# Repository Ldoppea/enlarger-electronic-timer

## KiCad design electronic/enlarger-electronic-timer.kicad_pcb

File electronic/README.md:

# Electronic for enlarger-electronic-timer

## Resources

Arduino Mini library downloaded from http://kicadhowto.org/LibLib.htm

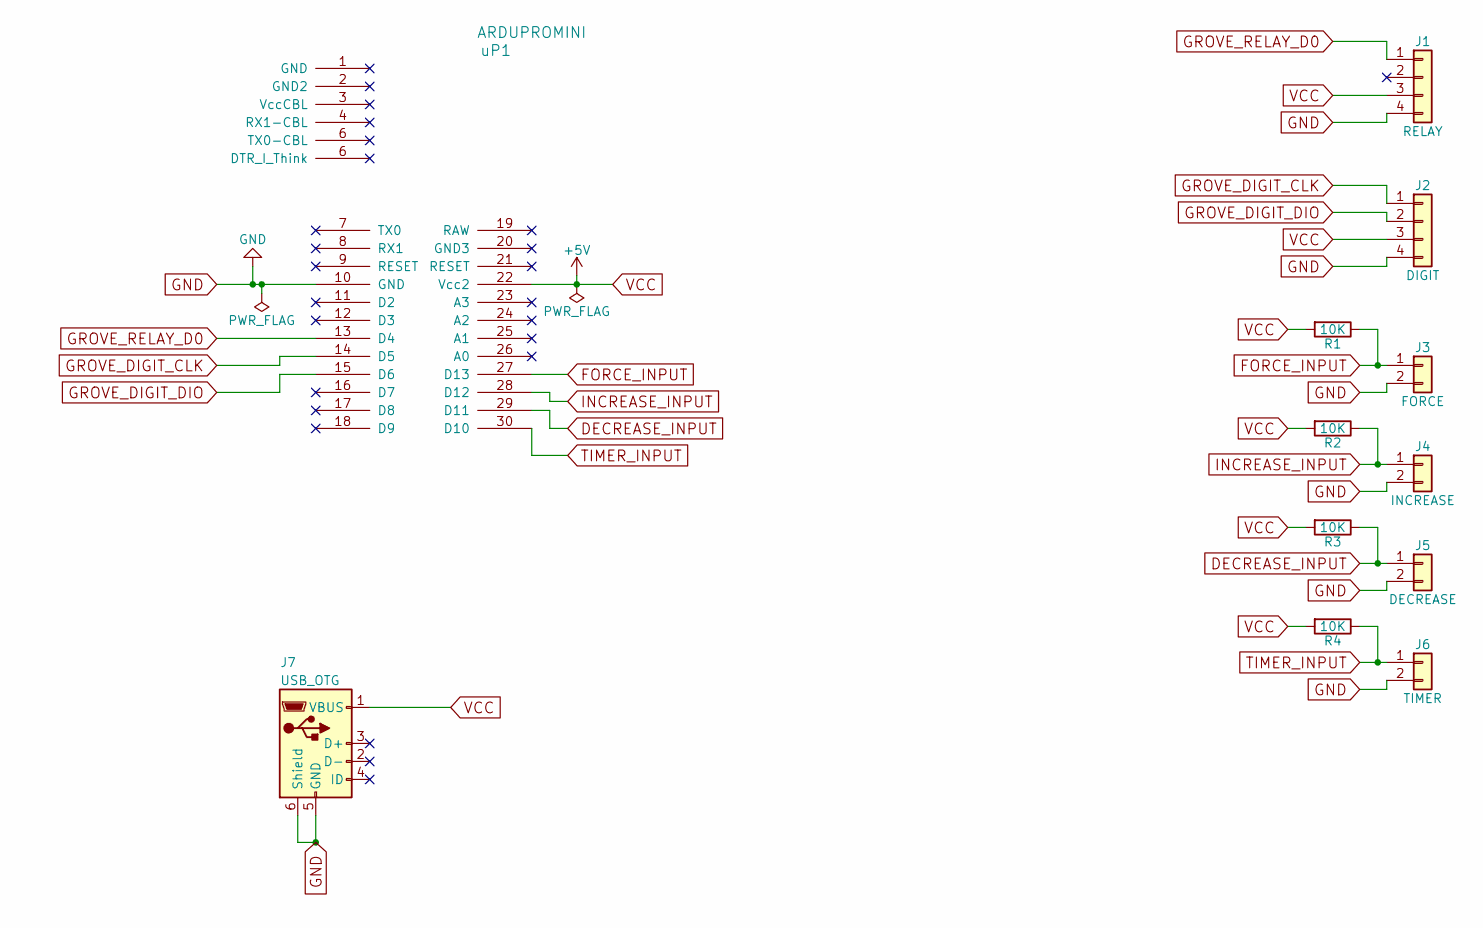
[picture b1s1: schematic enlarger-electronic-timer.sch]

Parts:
J1: RELAY; Grove_1x04
J2: DIGIT; Grove_1x04
J3: FORCE; Pin_Header_Straight_1x02_Pitch2.54mm
J4: INCREASE; Pin_Header_Straight_1x02_Pitch2.54mm
J5: DECREASE; Pin_Header_Straight_1x02_Pitch2.54mm
J6: TIMER; Pin_Header_Straight_1x02_Pitch2.54mm
J7: USB_OTG; ST-USB-013A
R1, R2, R3, R4: 10K; R_0603
uP1: ARDUPROMINI; arduino_mini

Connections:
DECREASE_INPUT: J5.1, R3.1, uP1.29 (D11)
FORCE_INPUT: J3.1, R1.1, uP1.27 (D13)
GND: J1.4, J2.4, J3.2, J4.2, J5.2, J6.2, J7.5 (GND), J7.6 (Shield), uP1.10 (GND)
GROVE_DIGIT_CLK: J2.1, uP1.14 (D5)
GROVE_DIGIT_DIO: J2.2, uP1.15 (D6)
GROVE_RELAY_D0: J1.1, uP1.13 (D4)
INCREASE_INPUT: J4.1, R2.1, uP1.28 (D12)
TIMER_INPUT: J6.1, R4.1, uP1.30 (D10)
VCC: J1.3, J2.3, J7.1 (VBUS), R1.2, R2.2, R3.2, R4.2, uP1.22 (Vcc2)

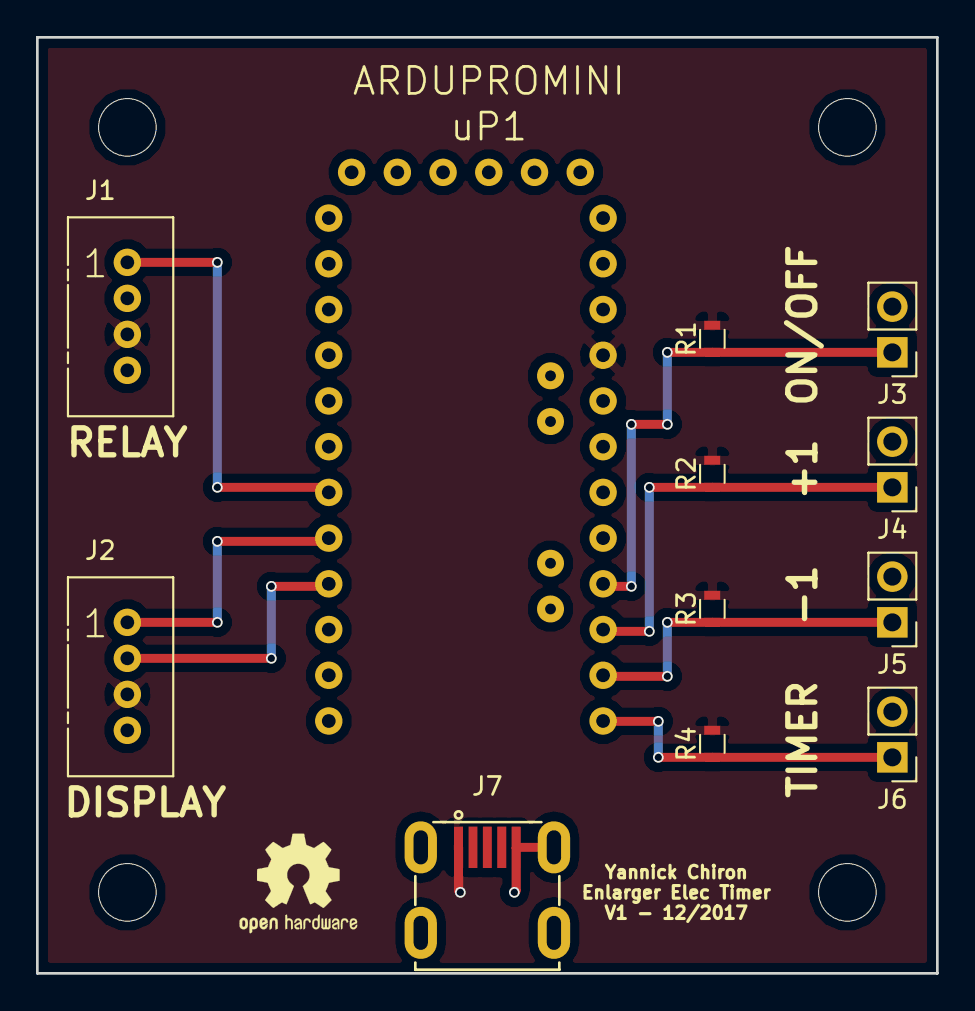
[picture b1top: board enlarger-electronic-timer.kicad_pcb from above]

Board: 2 copper layers, 50.0 x 52.0 mm, 12 parts (0 on the bottom side), 9 nets.

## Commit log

2017-12-16 Added Arduino Mini library
2017-12-16 Fixed arduino library power pins, added grov connectors for relay/digits
2017-12-16 Added buttons, USB. placed components on PCB
2017-12-16 Wired pcb
2017-12-16 Added dimensions
2017-12-17 Added link between USB GND pin and GND holes.
2017-12-17 Updated plot with latest changes
2017-12-17 Added OSHW loto and PCB name. Updated plot with latest changes
2019-04-10 Add CAD file for box 3D printing
2019-04-19 Increase M4 nuts sizes
2019-05-01 Decrease boxing size to fit 3D printer limitations
2019-05-01 Move top and bottom boxing into external sldprt files
2019-06-02 Add first draft for Arduino program
2019-06-02 Update timer to handle 2 different speeds
2019-06-02 Remove code comment
2019-06-03 Add timer run/pause/stop states
2019-06-03 Force if condition to compare with "true"
